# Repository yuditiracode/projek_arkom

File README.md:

Robot Line Follower Berbasis Mikrokontroler

Octaviant Dwi Ananda
- 25032014026

Yudi Tira Nanda Adi Saputra- 25032014010

https://youtu.be/lRbP8LNZPcw?si=ubMDkeoNteLDEgX2

 Deskripsi Proyek
Proyek ini merupakan implementasi embedded system berupa Robot Line Follower yang dirancang dan difabrikasi menggunakan PCB kustom. Robot menggunakan mikrokontroler ATmega328P (kompatibel Arduino Uno) sebagai otak utama untuk memproses sinyal dari 4 sensor inframerah (IR) dan mengatur gerakan dua motor DC melalui driver motor L293D.
Fitur Utama

4 Sensor IR Analog - deteksi posisi garis dengan resolusi 4-titik (kiri luar, kiri dalam, kanan dalam, kanan luar)
Kontrol PWM Motor - kecepatan motor diatur secara presisi melalui sinyal PWM (pin 9 & 10)
Algoritma Logika Bertingkat - 8 kondisi sensor diterjemahkan ke manuver: lurus, belok halus, belok tajam, belok sangat tajam, dan berhenti
PCB Kustom - desain skematik dan layout PCB menggunakan EAGLE CAD (.sch & .brd)
Debug Serial - output status sensor real-time via Serial Monitor (9600 baud)
Deteksi Persimpangan - robot berhenti otomatis saat semua sensor aktif (ujung jalur / persimpangan)

 Desain PCB
File desain PCB tersedia di folder src/:

.sch - Skematik rangkaian (buka dengan EAGLE atau KiCad)
.brd - Layout PCB siap fabrikasi (export ke Gerber untuk produksi)

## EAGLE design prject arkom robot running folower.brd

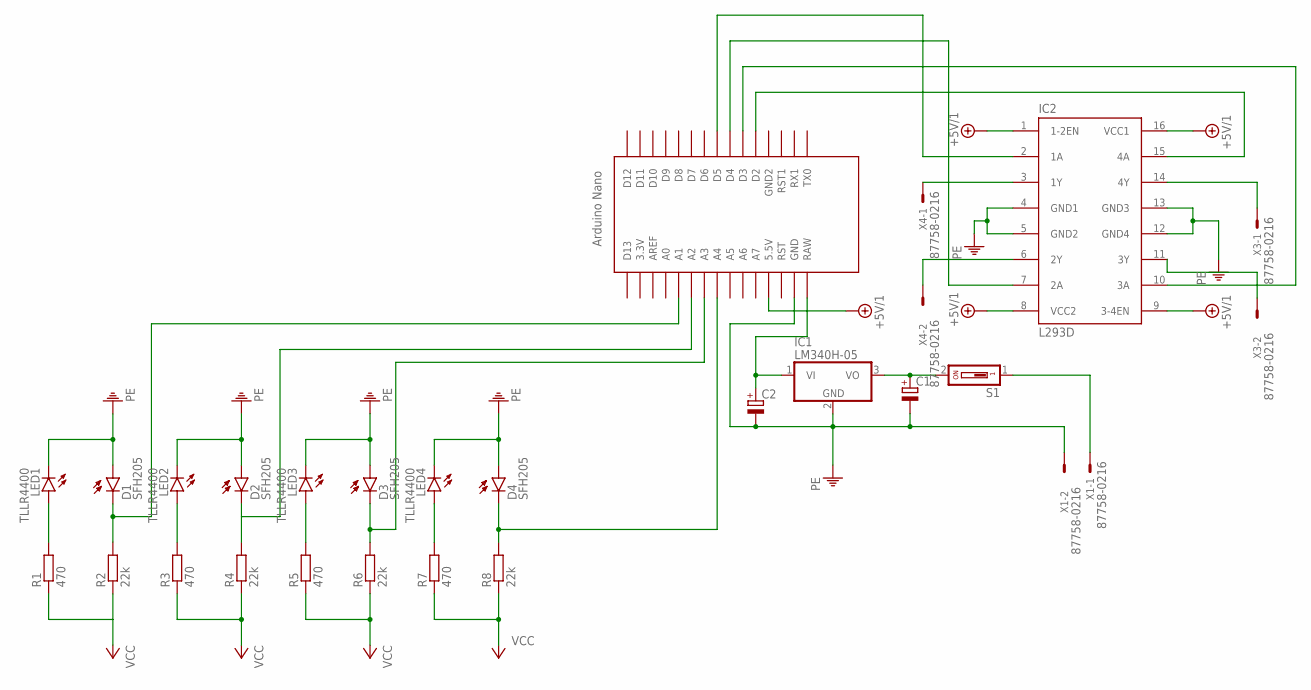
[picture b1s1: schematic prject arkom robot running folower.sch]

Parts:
C1, C2: CPOL-EUE2.5-7; E2,5-7
D1, D2, D3, D4: SFH205
IC1: LM340H-05; TO220H
IC2: L293D; DIL16
LED1, LED2, LED3, LED4: TLLR4400; LED3MM
R1, R3, R5, R7: 470; 0204/7
R2, R4, R6, R8: 22k; 0204/7
S1: SD4-01
U$1: NANO
X1, X3, X4: 87758-0216

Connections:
+5V/1: IC2.1 (1-2EN), IC2.8 (VCC2), IC2.9 (3-4EN), IC2.16 (VCC1), U$1.5V (5.5V)
unnamed: S1.1, X1.1
unnamed: C1.+, IC1.3 (VO), S1.2
unnamed: C2.+, IC1.1 (VI), U$1.RAW
unnamed: IC2.3 (1Y), X4.1
unnamed: LED1.A, R1.2
unnamed: D1.K (C), R2.2, U$1.A1
unnamed: LED2.A, R3.2
unnamed: D2.K (C), R4.2, U$1.A2
unnamed: LED3.A, R5.2
unnamed: D3.K (C), R6.2, U$1.A3
unnamed: LED4.A, R7.2
unnamed: D4.K (C), R8.2, U$1.A4
unnamed: IC2.6 (2Y), X4.2
unnamed: IC2.14 (4Y), X3.1
unnamed: IC2.11 (3Y), X3.2
unnamed: IC2.15 (4A), U$1.D2
unnamed: IC2.10 (3A), U$1.D3
unnamed: IC2.7 (2A), U$1.D4
unnamed: IC2.2 (1A), U$1.D5
PE: C1.-, C2.-, D1.A, D2.A, D3.A, D4.A, IC1.2 (GND), IC2.4 (GND1), IC2.5 (GND2), IC2.12 (GND4), IC2.13 (GND3), LED1.K (C), LED2.K (C), LED3.K (C), LED4.K (C), U$1.GND, X1.2
VCC: R1.1, R2.1, R3.1, R4.1, R5.1, R6.1, R7.1, R8.1

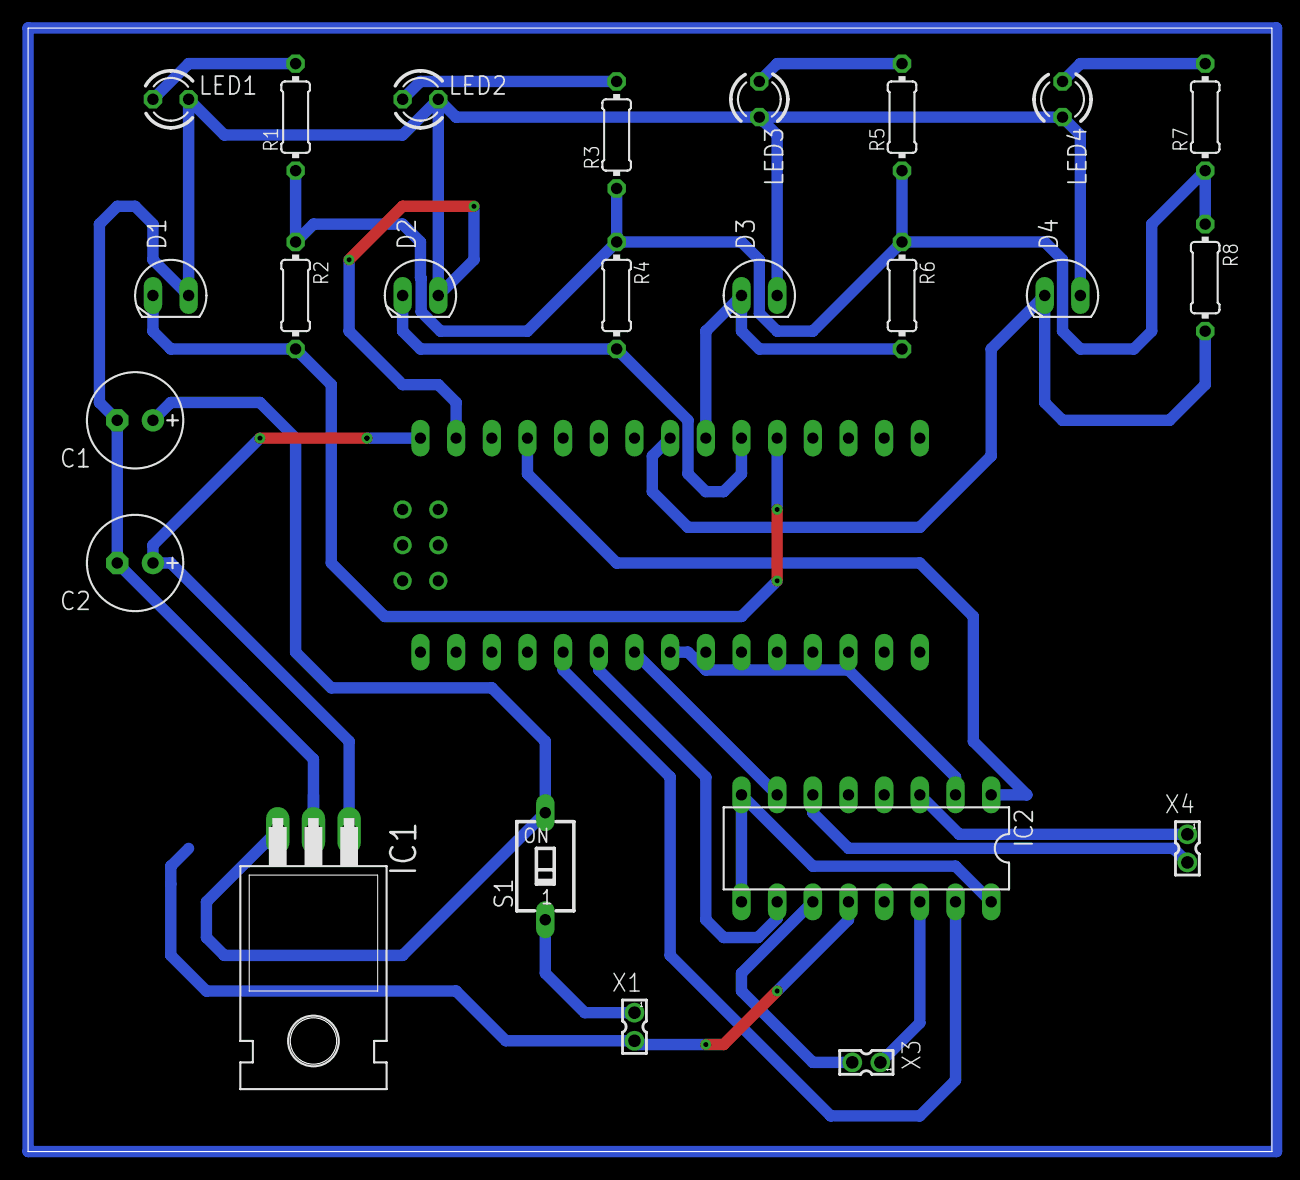
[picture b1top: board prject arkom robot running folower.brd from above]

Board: 2 copper layers, 88.6 x 80.0 mm, 25 parts (0 on the bottom side), 22 nets.

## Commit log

2026-05-28 projek_arkom
